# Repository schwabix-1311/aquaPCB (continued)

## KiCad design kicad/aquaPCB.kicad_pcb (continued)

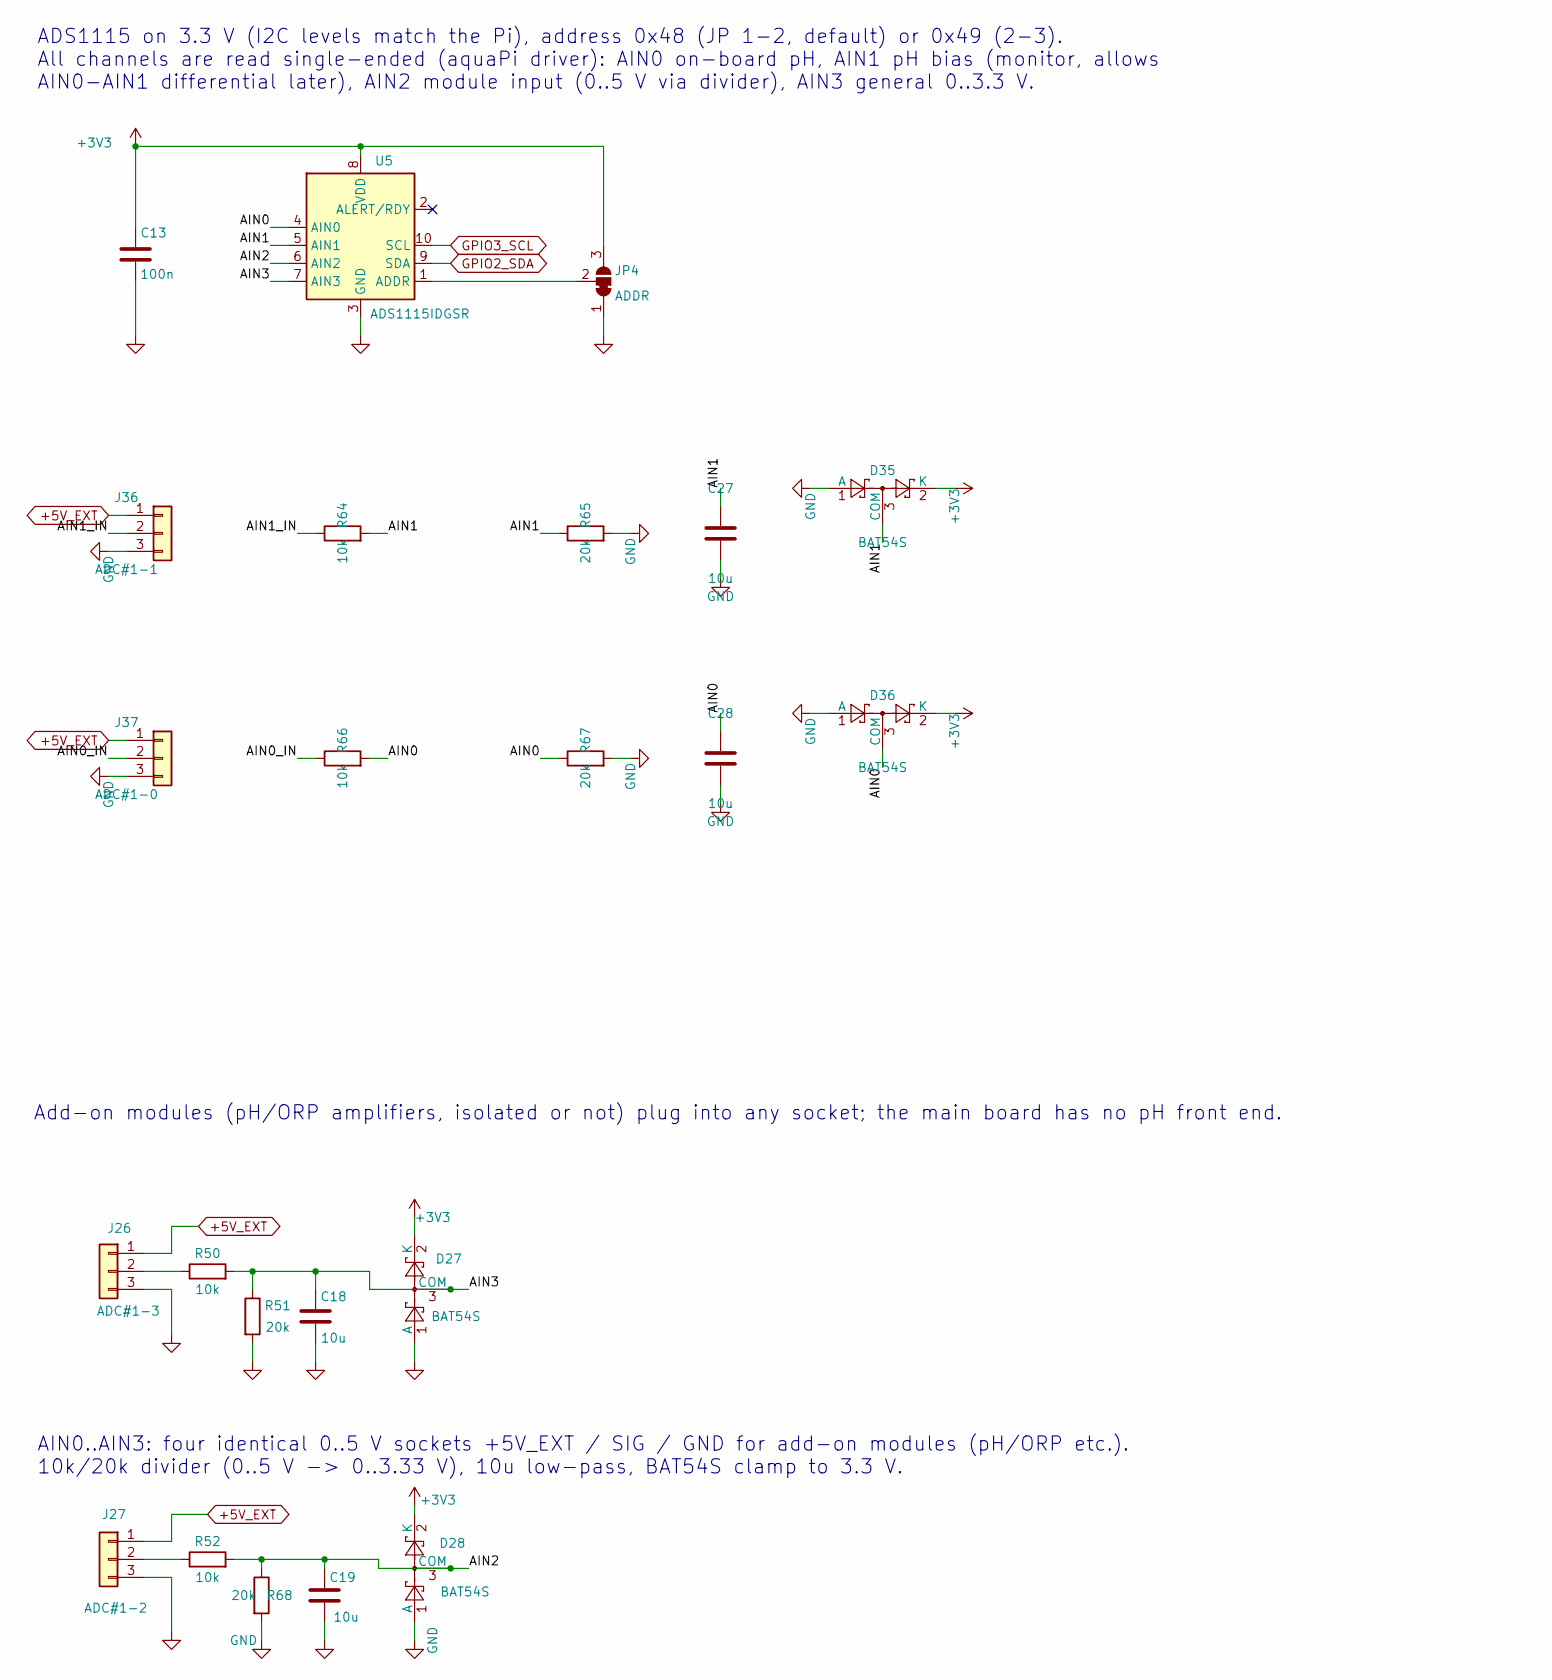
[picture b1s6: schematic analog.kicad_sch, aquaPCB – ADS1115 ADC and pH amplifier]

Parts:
C13: 100n; C_0805_2012Metric; LCSC C49678
C18, C19, C27, C28: 10u; C_0805_2012Metric; LCSC C15850
D27, D28, D35, D36: BAT54S; SOT-23; LCSC C7420333
J26: ADC#1-3; PinHeader_1x03_P2.54mm_Vertical
J27: ADC#1-2; PinHeader_1x03_P2.54mm_Vertical
J36: ADC#1-1; PinHeader_1x03_P2.54mm_Vertical
J37: ADC#1-0; PinHeader_1x03_P2.54mm_Vertical
JP4: ADDR; SolderJumper-3_P1.3mm_Bridged12_RoundedPad1.0x1.5mm
R50, R52, R64, R66: 10k; R_0805_2012Metric; LCSC C17414
R51, R65, R67, R68: 20k; R_0805_2012Metric; LCSC C4328
U5: ADS1115IDGSR; TSSOP-10_3x3mm_P0.5mm; LCSC C37593

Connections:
+3V3: C13.1, D27.2 (K), D28.2 (K), D35.2 (K), D36.2 (K), JP4.3 (B), U5.8 (VDD); also elsewhere on the board
+5V_EXT: J26.1, J27.1, J36.1, J37.1; also elsewhere on the board
/ADS1115 ADC and analog sockets/AIN0: C28.1, D36.3 (COM), R66.2, R67.1, U5.4 (AIN0)
/ADS1115 ADC and analog sockets/AIN0_IN: J37.2, R66.1
/ADS1115 ADC and analog sockets/AIN1: C27.1, D35.3 (COM), R64.2, R65.1, U5.5 (AIN1)
/ADS1115 ADC and analog sockets/AIN1_IN: J36.2, R64.1
/ADS1115 ADC and analog sockets/AIN2: C19.1, D28.3 (COM), R52.2, R68.1, U5.6 (AIN2)
/ADS1115 ADC and analog sockets/AIN3: C18.1, D27.3 (COM), R50.2, R51.1, U5.7 (AIN3)
GND: C13.2, C18.2, C19.2, C27.2, C28.2, D27.1 (A), D28.1 (A), D35.1 (A), D36.1 (A), J26.3, J27.3, J36.3, J37.3, JP4.1 (A), R51.2, R65.2, R67.2, R68.2, U5.3 (GND); also elsewhere on the board
GPIO2_SDA: U5.9 (SDA); also elsewhere on the board
GPIO3_SCL: U5.10 (SCL); also elsewhere on the board
unnamed: J26.2, R50.1
unnamed: J27.2, R52.1
unnamed: JP4.2 (C), U5.1 (ADDR)

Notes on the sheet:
AIN0..AIN3: four identical 0..5 V sockets +5V_EXT / SIG / GND for add-on modules (pH/ORP etc.). 10k/20k divider (0..5 V -> 0..3.33 V), 10u low-pass, BAT54S clamp to 3.3 V.
Add-on modules (pH/ORP amplifiers, isolated or not) plug into any socket; the main board has no pH front end.
ADS1115 on 3.3 V (I2C levels match the Pi), address 0x48 (JP 1-2, default) or 0x49 (2-3). All channels are read single-ended (aquaPi driver): AIN0 on-board pH, AIN1 pH bias (monitor, allows AIN0-AIN1 differential later), AIN2 module input (0..5 V via divider), AIN3 general 0..3.3 V.

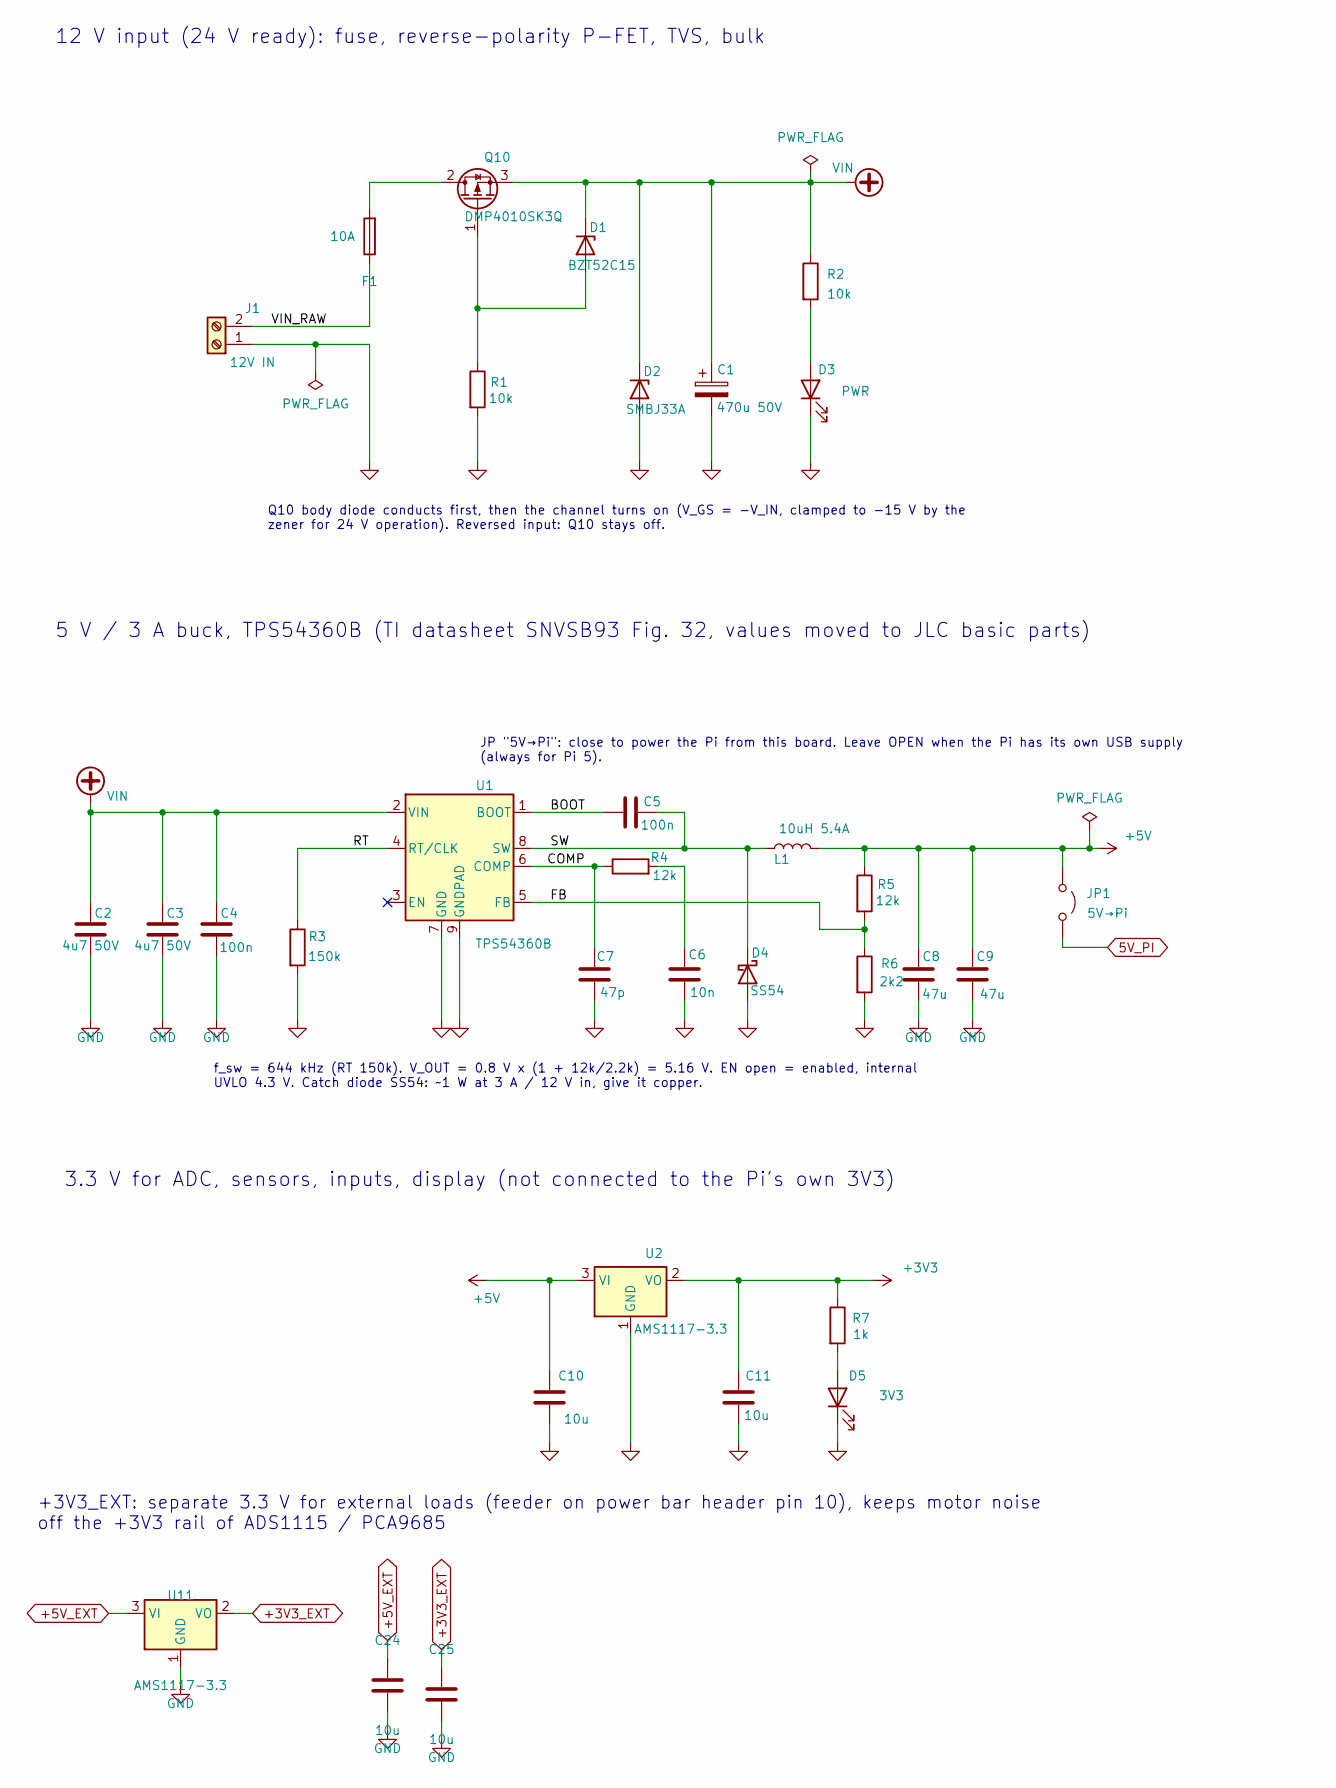
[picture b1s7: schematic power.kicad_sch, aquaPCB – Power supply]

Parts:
C1: 470u 50V; CP_Radial_D10.0mm_P5.00mm; MPN Rubycon 50ZLJ470M10X20
C2, C3: 4u7 50V; C_1206_3216Metric; LCSC C29823
C4, C5: 100n; C_0805_2012Metric; LCSC C49678
C6: 10n; C_0805_2012Metric; LCSC C1710
C7: 47p; C_0805_2012Metric; LCSC C14857
C8, C9: 47u; C_1206_3216Metric; LCSC C96123
C10, C11, C24, C25: 10u; C_0805_2012Metric; LCSC C15850
D1: BZT52C15; D_SOD-123; LCSC C19077412
D2: SMBJ33A; D_SMB; LCSC C19077586
D3: PWR; LED_0805_2012Metric; LCSC C84256
D4: SS54; D_SMA; LCSC C22452
D5: 3V3; LED_0805_2012Metric; LCSC C2297
F1: 10A; Littelfuse_OMNI-BLOK_154; LCSC C206921
J1: 12V IN; TerminalBlock_Kangnex_WJ250B-3.5-02P_P3.50mm_Staggered; LCSC C8454
JP1: 5V→Pi; PinHeader_1x02_P2.54mm_Vertical
L1: 10uH 5.4A; L_SLF12565_CDRH127; LCSC C9904
Q10: DMP4010SK3Q; TO-252-2; LCSC C5359358
R1, R2: 10k; R_0805_2012Metric; LCSC C17414
R3: 150k; R_0805_2012Metric; LCSC C17470
R4, R5: 12k; R_0805_2012Metric; LCSC C17444
R6: 2k2; R_0805_2012Metric; LCSC C17520
R7: 1k; R_0805_2012Metric; LCSC C17513
U1: TPS54360B; TI_SO-PowerPAD-8_ThermalVias; LCSC C524806
U2, U11: AMS1117-3.3; SOT-223-3_TabPin2; LCSC C6186

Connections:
5V_PI: JP1.2 (B); also elsewhere on the board
+3V3: C11.1, R7.1, U2.2 (VO); also elsewhere on the board
+3V3_EXT: C25.1, U11.2 (VO); also elsewhere on the board
+5V: C8.1, C9.1, C10.1, JP1.1 (A), L1.2, R5.1, U2.3 (VI); also elsewhere on the board
+5V_EXT: C24.1, U11.3 (VI); also elsewhere on the board
/Power supply/BOOT: C5.1, U1.1 (BOOT)
/Power supply/COMP: C7.1, R4.1, U1.6 (COMP)
/Power supply/FB: R5.2, R6.1, U1.5 (FB)
/Power supply/RT: R3.1, U1.4 (RT/CLK)
/Power supply/SW: C5.2, D4.1 (K), L1.1, U1.8 (SW)
/Power supply/VIN_RAW: F1.1, J1.2
GND: C1.2, C2.2, C3.2, C4.2, C6.2, C7.2, C8.2, C9.2, C10.2, C11.2, C24.2, C25.2, D2.2 (A), D3.1 (K), D4.2 (A), D5.1 (K), J1.1, R1.2, R3.2, R6.2, U1.7 (GND), U1.9 (GNDPAD), U2.1 (GND), U11.1 (GND); also elsewhere on the board
unnamed: C6.1, R4.2
unnamed: D1.2 (A), Q10.1 (G), R1.1
unnamed: D3.2 (A), R2.2
unnamed: D5.2 (A), R7.2
unnamed: F1.2, Q10.2 (D)
VIN: C1.1, C2.1, C3.1, C4.1, D1.1 (K), D2.1 (K), Q10.3 (S), R2.1, U1.2 (VIN); also elsewhere on the board

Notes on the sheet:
5 V / 3 A buck, TPS54360B (TI datasheet SNVSB93 Fig. 32, values moved to JLC basic parts)
f_sw = 644 kHz (RT 150k). V_OUT = 0.8 V x (1 + 12k/2.2k) = 5.16 V. EN open = enabled, internal UVLO 4.3 V. Catch diode SS54: ~1 W at 3 A / 12 V in, give it copper.
JP "5V→Pi": close to power the Pi from this board. Leave OPEN when the Pi has its own USB supply (always for Pi 5).
Q10 body diode conducts first, then the channel turns on (V_GS = -V_IN, clamped to -15 V by the zener for 24 V operation). Reversed input: Q10 stays off.
12 V input (24 V ready): fuse, reverse-polarity P-FET, TVS, bulk
3.3 V for ADC, sensors, inputs, display (not connected to the Pi's own 3V3)
+3V3_EXT: separate 3.3 V for external loads (feeder on power bar header pin 10), keeps motor noise off the +3V3 rail of ADS1115 / PCA9685

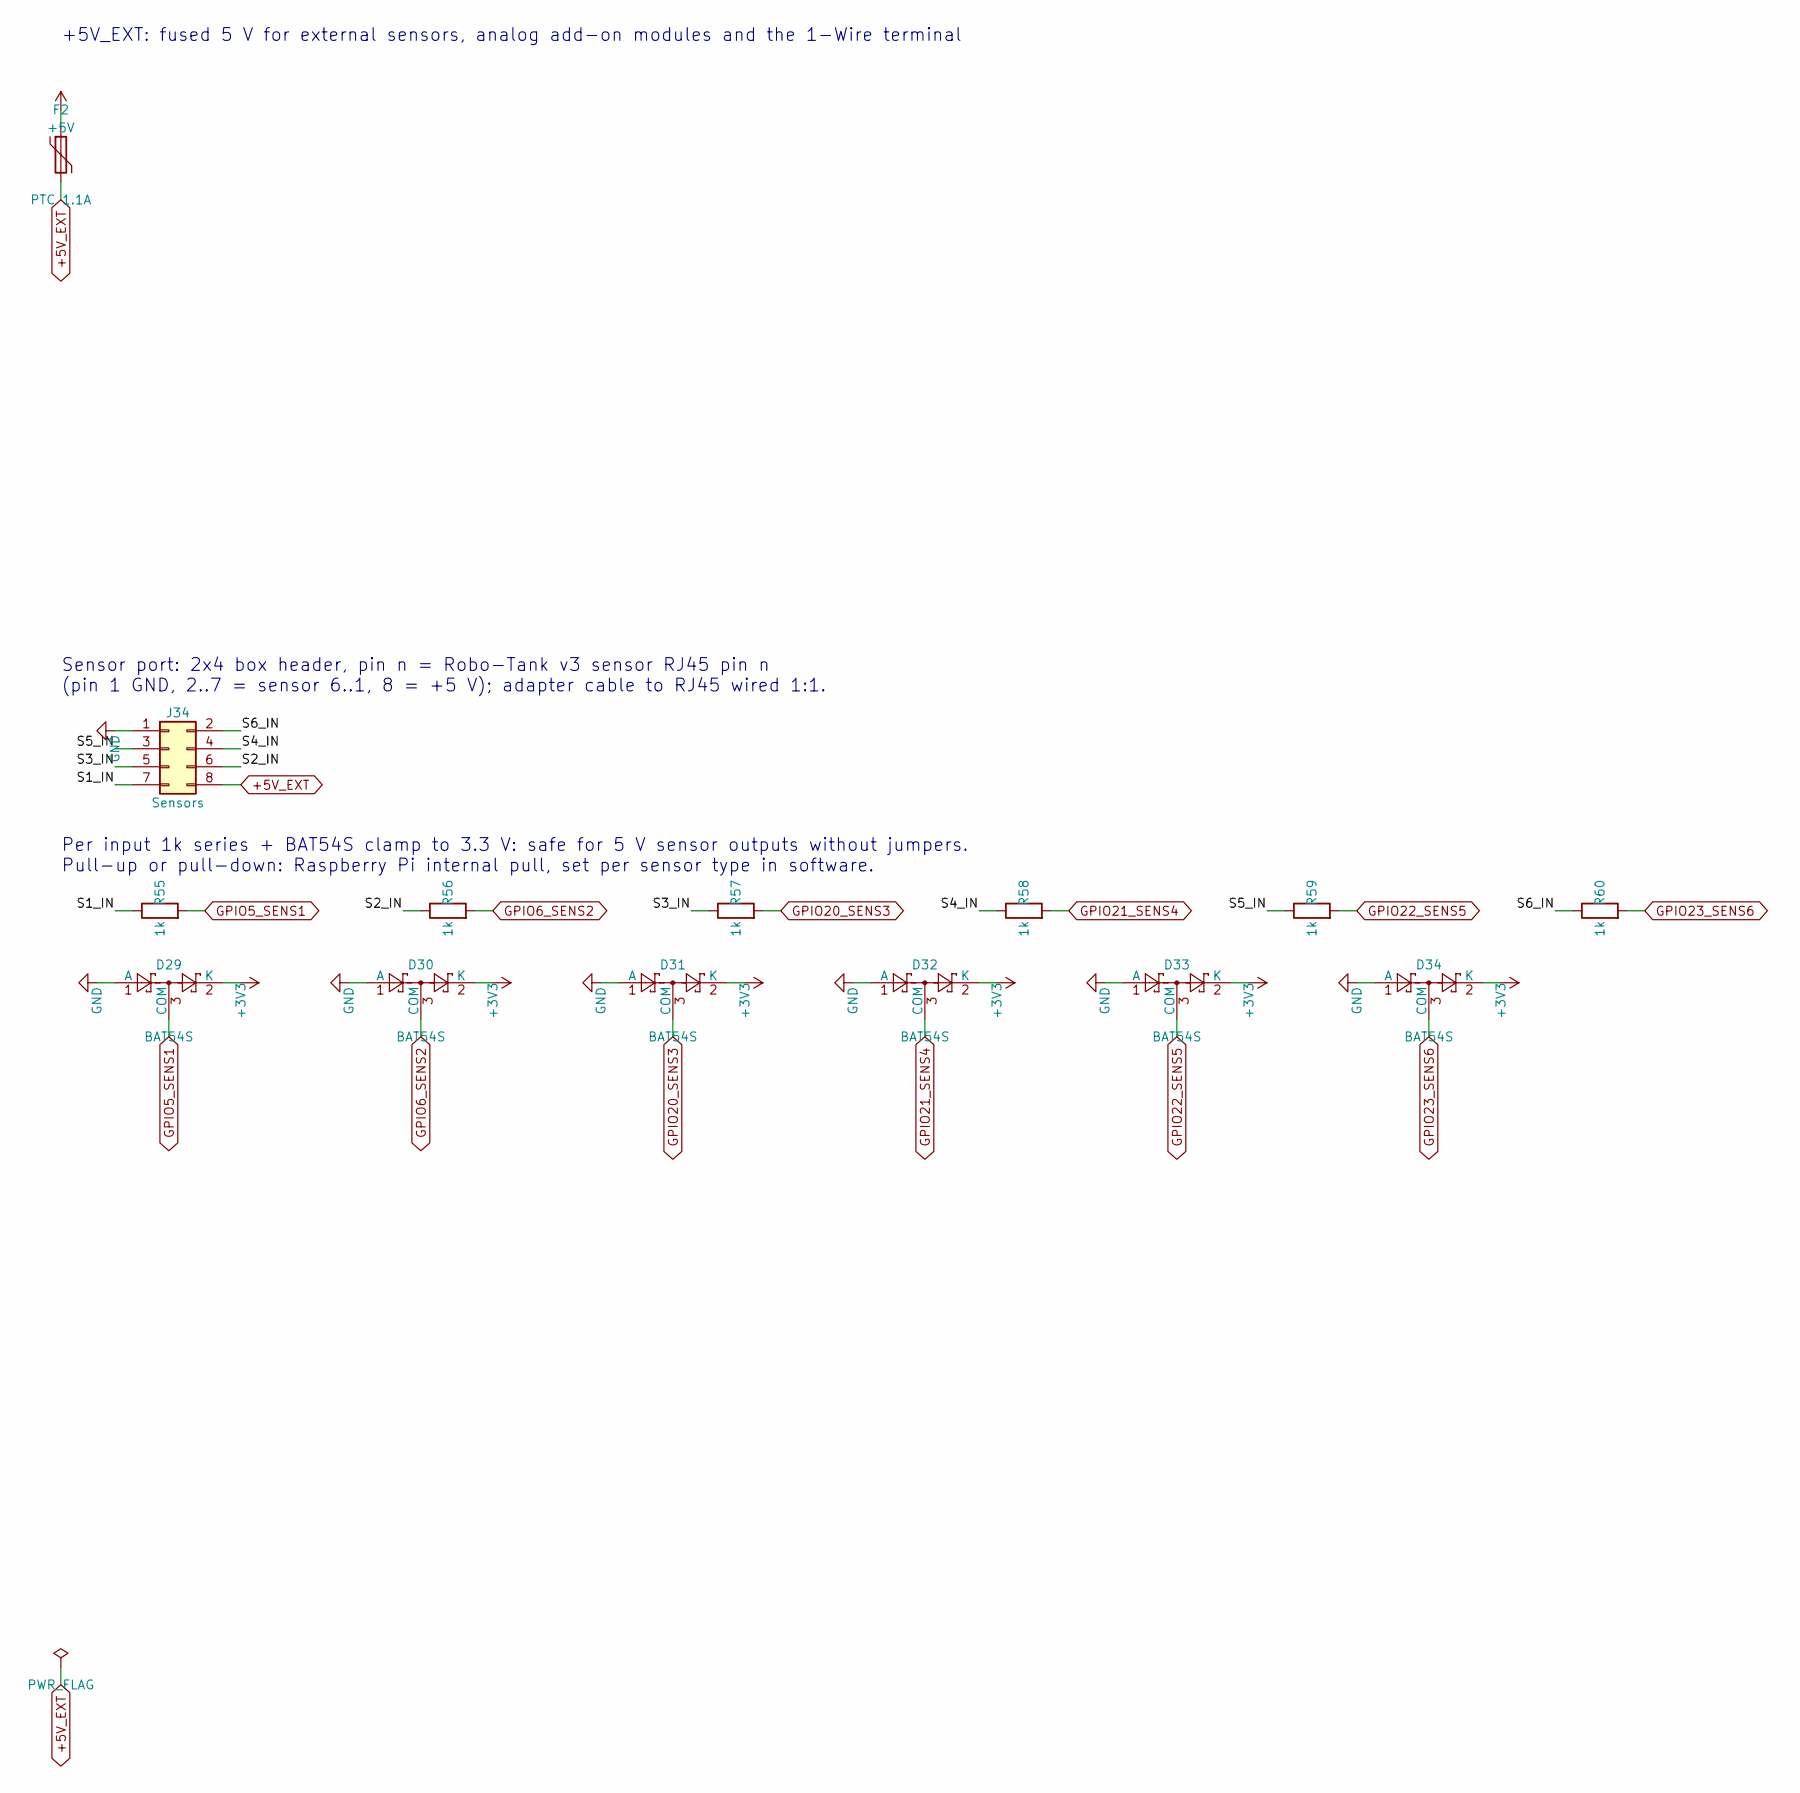
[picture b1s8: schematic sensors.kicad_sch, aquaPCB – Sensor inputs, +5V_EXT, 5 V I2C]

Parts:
D29, D30, D31, D32, D33, D34: BAT54S; SOT-23; LCSC C7420333
F2: PTC 1.1A; Fuse_1206_3216Metric; LCSC C71465
J34: Sensors; IDC-Header_2x04_P2.54mm_Vertical
R55, R56, R57, R58, R59, R60: 1k; R_0805_2012Metric; LCSC C17513

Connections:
+3V3: D29.2 (K), D30.2 (K), D31.2 (K), D32.2 (K), D33.2 (K), D34.2 (K); also elsewhere on the board
+5V: F2.1; also elsewhere on the board
+5V_EXT: F2.2, J34.8; also elsewhere on the board
/Sensor inputs, +5V_EXT/S1_IN: J34.7, R55.1
/Sensor inputs, +5V_EXT/S2_IN: J34.6, R56.1
/Sensor inputs, +5V_EXT/S3_IN: J34.5, R57.1
/Sensor inputs, +5V_EXT/S4_IN: J34.4, R58.1
/Sensor inputs, +5V_EXT/S5_IN: J34.3, R59.1
/Sensor inputs, +5V_EXT/S6_IN: J34.2, R60.1
GND: D29.1 (A), D30.1 (A), D31.1 (A), D32.1 (A), D33.1 (A), D34.1 (A), J34.1; also elsewhere on the board
GPIO5_SENS1: D29.3 (COM), R55.2; also elsewhere on the board
GPIO6_SENS2: D30.3 (COM), R56.2; also elsewhere on the board
GPIO20_SENS3: D31.3 (COM), R57.2; also elsewhere on the board
GPIO21_SENS4: D32.3 (COM), R58.2; also elsewhere on the board
GPIO22_SENS5: D33.3 (COM), R59.2; also elsewhere on the board
GPIO23_SENS6: D34.3 (COM), R60.2; also elsewhere on the board

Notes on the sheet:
+5V_EXT: fused 5 V for external sensors, analog add-on modules and the 1-Wire terminal
Sensor port: 2x4 box header, pin n = Robo-Tank v3 sensor RJ45 pin n (pin 1 GND, 2..7 = sensor 6..1, 8 = +5 V); adapter cable to RJ45 wired 1:1.
Per input 1k series + BAT54S clamp to 3.3 V: safe for 5 V sensor outputs without jumpers. Pull-up or pull-down: Raspberry Pi internal pull, set per sensor type in software.

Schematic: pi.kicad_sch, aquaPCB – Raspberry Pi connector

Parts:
H1, H2, H3, H4: M3; MountingHole_3.2mm_M3
H5, H6: M2.5 Pi Zero; MountingHole_2.7mm_M2.5
J2: Raspberry Pi; IDC-Header_2x20_P2.54mm_Vertical

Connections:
5V_PI: J2.2, J2.4; also elsewhere on the board
GND: J2.6, J2.9, J2.14, J2.20, J2.25, J2.30, J2.34, J2.39; also elsewhere on the board
GPIO2_SDA: J2.3; also elsewhere on the board
GPIO3_SCL: J2.5; also elsewhere on the board
GPIO4_1W: J2.7; also elsewhere on the board
GPIO5_SENS1: J2.29; also elsewhere on the board
GPIO6_SENS2: J2.31; also elsewhere on the board
GPIO7_CE1: J2.26; also elsewhere on the board
GPIO8_CE0: J2.24; also elsewhere on the board
GPIO9_MISO: J2.21; also elsewhere on the board
GPIO10_MOSI: J2.19; also elsewhere on the board
GPIO11_SCLK: J2.23; also elsewhere on the board
GPIO12_Q6: J2.32; also elsewhere on the board
GPIO13_Q5: J2.33; also elsewhere on the board
GPIO16_Q2: J2.36; also elsewhere on the board
GPIO18_Q1: J2.12; also elsewhere on the board
GPIO19_Q4: J2.35; also elsewhere on the board
GPIO20_SENS3: J2.38; also elsewhere on the board
GPIO21_SENS4: J2.40; also elsewhere on the board
GPIO22_SENS5: J2.15; also elsewhere on the board
GPIO23_SENS6: J2.16; also elsewhere on the board
GPIO24_DISP_RST: J2.18; also elsewhere on the board
GPIO25_DISP_DC: J2.22; also elsewhere on the board
GPIO26_Q3: J2.37; also elsewhere on the board

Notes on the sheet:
40-pin Pi header, normal (not mirrored) numbering. Fit 2x20 socket (Pi Zero 2 W face-up, header soldered on its underside) or 40-pin box header (Pi 3/4 via IDC ribbon).
Pins 1/17 (Pi 3V3) stay unconnected: this board has its own 3.3 V regulator. Pins 27/28 (ID EEPROM) unused. GPIO 14/15 only go to the UART console header.

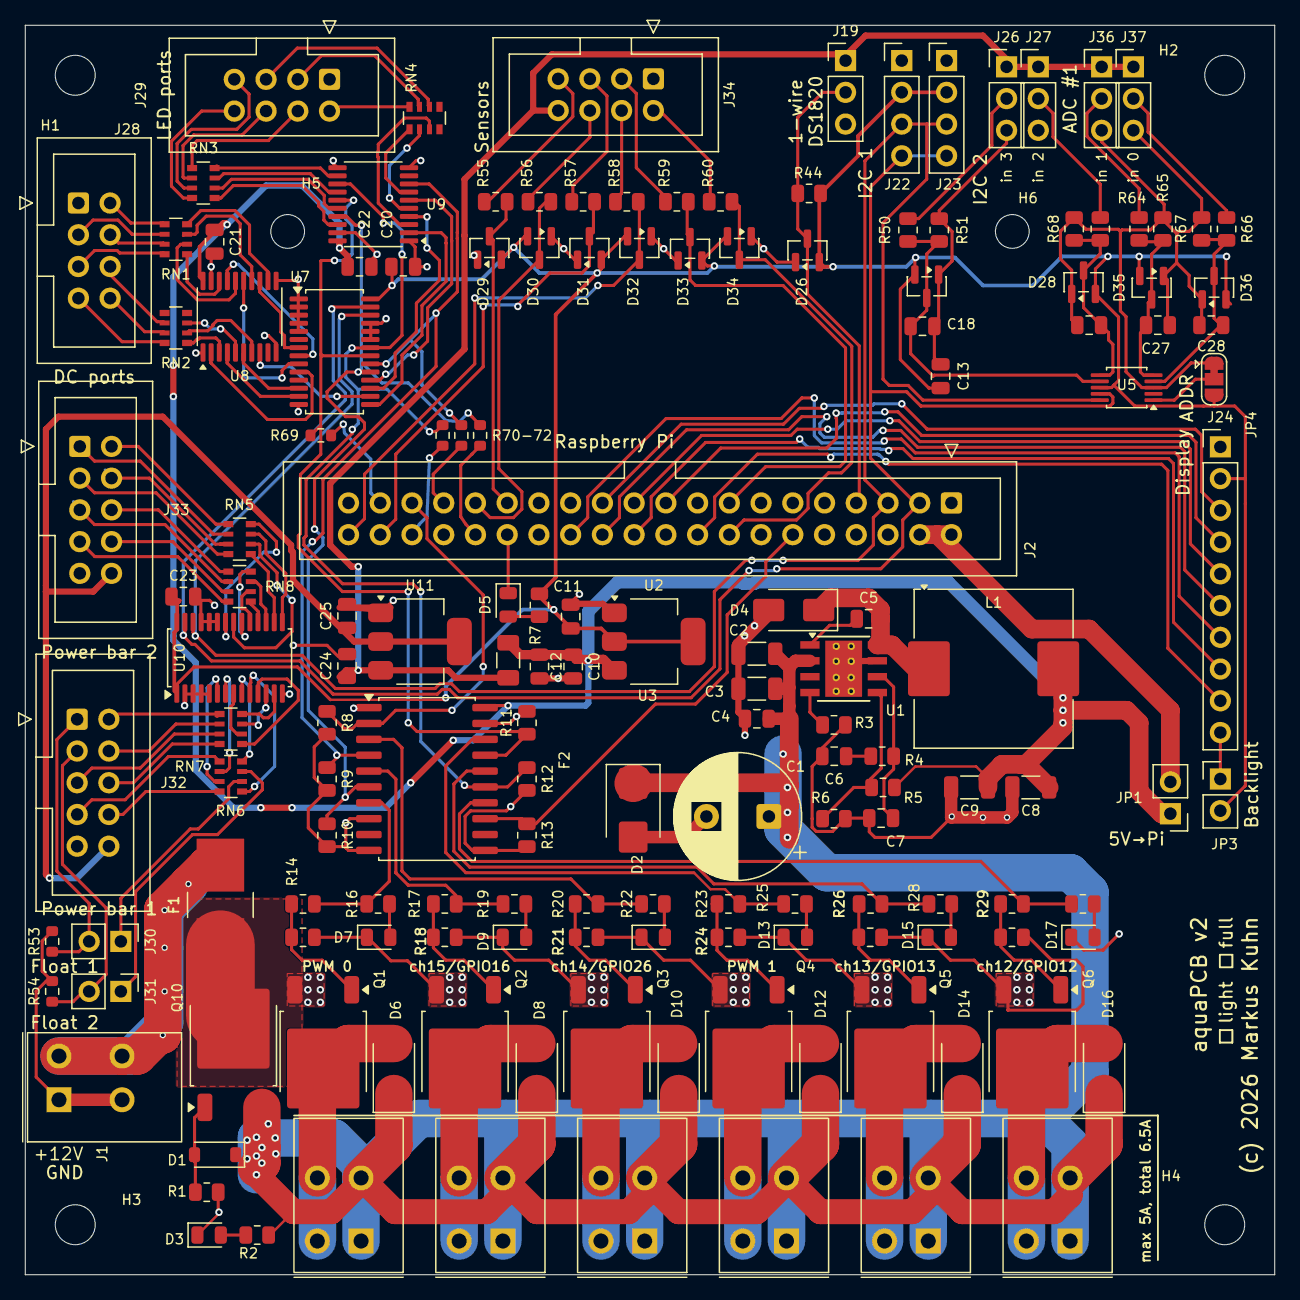
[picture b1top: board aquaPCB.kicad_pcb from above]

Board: 2 copper layers, 100.0 x 100.0 mm, 162 parts (0 on the bottom side), 156 nets.

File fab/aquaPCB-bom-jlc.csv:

Comment,Designator,Footprint,LCSC Part #
4u7 50V,"C2,C3",C_1206_3216Metric,C29823
100n,"C4,C5,C12,C13,C20,C21,C22,C23",C_0805_2012Metric,C49678
10n,C6,C_0805_2012Metric,C1710
47p,C7,C_0805_2012Metric,C14857
47u,"C8,C9",C_1206_3216Metric,C96123
10u,"C10,C11,C18,C19,C24,C25,C27,C28",C_0805_2012Metric,C15850
BZT52C15,D1,D_SOD-123,C19077412
SMBJ33A,D2,D_SMB,C19077586
PWR,D3,LED_0805_2012Metric,C84256
SS54,"D4,D6,D8,D10,D12,D14,D16",D_SMA,C22452
3V3,D5,LED_0805_2012Metric,C2297
GPIO18,D7,LED_0805_2012Metric,C2297
PCA#1 ch15,D9,LED_0805_2012Metric,C2297
PCA#1 ch14,D11,LED_0805_2012Metric,C2297
GPIO19,D13,LED_0805_2012Metric,C2297
PCA#1 ch13,D15,LED_0805_2012Metric,C2297
PCA#1 ch12,D17,LED_0805_2012Metric,C2297
BAT54S,"D26,D27,D28,D29,D30,D31,D32,D33,D34,D35,D36",SOT-23,C7420333
10A,F1,Littelfuse_OMNI-BLOK_154,C206921
PTC 1.1A,F2,Fuse_1206_3216Metric,C71465
10uH 5.4A,L1,L_SLF12565_CDRH127,C9904
AOD4184A,"Q1,Q2,Q3,Q4,Q5,Q6",TO-252-2,C99124
DMP4010SK3Q,Q10,TO-252-2,C5359358
10k,"R1,R2,R8,R9,R10,R11,R12,R13,R15,R18,R21,R24,R27,R30,R50,R52,R64,R66",R_0805_2012Metric,C17414
150k,R3,R_0805_2012Metric,C17470
12k,"R4,R5",R_0805_2012Metric,C17444
2k2,R6,R_0805_2012Metric,C17520
1k,"R7,R16,R19,R22,R25,R28,R31,R55,R56,R57,R58,R59,R60",R_0805_2012Metric,C17513
100,"R14,R17,R20,R23,R26,R29",R_0805_2012Metric,C17408
4k7,R44,R_0805_2012Metric,C17673
20k,"R51,R65,R67,R68",R_0805_2012Metric,C4328
10k,"R53,R54",R_0603_1608Metric,C25804
4x100,"RN1,RN2,RN3,RN4,RN5,RN6,RN7,RN8",R_Array_Convex_4x0603,C25506
TPS54360B,U1,TI_SO-PowerPAD-8_ThermalVias,C524806
AMS1117-3.3,"U2,U11",SOT-223-3_TabPin2,C6186
74HCT244D,U3,SOIC-20W_7.5x12.8mm_P1.27mm,C5978
ADS1115IDGSR,U5,TSSOP-10_3x3mm_P0.5mm,C37593
PCA9685PW,"U7,U10",TSSOP-28_4.4x9.7mm_P0.65mm,C2678753
74HCT244PW,"U8,U9",TSSOP-20_4.4x6.5mm_P0.65mm,C131088

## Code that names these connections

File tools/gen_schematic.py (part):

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sh.note('40-pin Pi header, normal (not mirrored) numbering. Fit 2x20 socket (Pi Zero 2 W face-up, header\n'
        'soldered on its underside) or 40-pin box header (Pi 3/4 via IDC ribbon).', 2)
pi_pins = {
    1: NC, 2: '5V_PI', 3: 'GPIO2_SDA', 4: '5V_PI', 5: 'GPIO3_SCL', 6: 'GND', 7: 'GPIO4_1W', 8: 'GPIO14_TXD',
    9: 'GND', 10: 'GPIO15_RXD', 11: 'GPIO17_S1', 12: 'GPIO18_Q1', 13: 'GPIO27_S4', 14: 'GND',
    15: 'GPIO22_S2', 16: 'GPIO23_S3', 17: NC, 18: 'GPIO24_DISP_RST', 19: 'GPIO10_MOSI', 20: 'GND',
    21: 'GPIO9_MISO', 22: 'GPIO25_DISP_DC', 23: 'GPIO11_SCLK', 24: 'GPIO8_CE0', 25: 'GND', 26: 'GPIO7_CE1',
    27: NC, 28: NC, 29: 'GPIO5_IN1', 30: 'GND', 31: 'GPIO6_IN2', 32: 'GPIO12_Q3', 33: 'GPIO13_Q4', 34: 'GND',
    35: 'GPIO19_Q2', 36: 'GPIO16_Q5', 37: 'GPIO26_Q6', 38: 'GPIO20_IN3', 39: 'GND', 40: 'GPIO21_IN4'}
jpi = sh.part('Connector_Generic:Conn_02x20_Odd_Even', 'J', 'Raspberry Pi',
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# ================================================================ Power outputs
sh = p.sheet('outputs', 'outputs.kicad_sch', 'Power outputs Q1..Q6')
sh.note('74HCT244 shifts 3.3 V GPIO to 5 V gate drive and isolates the Pi from the power stage.', 2)
gpio_q = ['GPIO18_Q1', 'GPIO19_Q2', 'GPIO12_Q3', 'GPIO13_Q4', 'GPIO16_Q5', 'GPIO26_Q6']
buf = sh.part('74xx:74HCT244', 'U', '74HCT244D', {
    '1': 'GND', '19': 'GND', '20': '+5V', '10': 'GND',
    '2': gpio_q[0], '4': gpio_q[1], '6': gpio_q[2], '8': gpio_q[3],
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    rp = R(sh, '10k', '+3V3', g)
    sh.row([t, rs, rp, clamp(sh, g)])
sh.note('1-Wire (DS18B20), GPIO4, 4.7k pull-up. Terminal: GND / DQ / 3V3; parasitic sensors use GND + DQ.', 2)
r1w = R(sh, '4k7', '+3V3', 'GPIO4_1W')
terms = [term(sh, ['GND', 'GPIO4_1W', '+3V3'], f'1-Wire {i}') for i in range(1, 3)]
sh.row([r1w, clamp(sh, 'GPIO4_1W')] + terms)
sh.note('I2C expansion (OLED, PCA9685, ...), SSD1306 pin order. Pull-ups are on the Pi (1.8k).', 2)
i2c = [header(sh, ['GND', '+3V3', 'GPIO3_SCL', 'GPIO2_SDA'], f'I2C {i}') for i in (1, 2)]
sh.row(i2c)
sh.note('SPI display (ST7735 / ILI9341). Backlight to 3V3 via jumper.', 2)
disp = header(sh, ['GND', '+3V3', 'GPIO11_SCLK', 'GPIO10_MOSI', 'GPIO9_MISO', 'GPIO8_CE0', 'GPIO7_CE1',
                   'GPIO25_DISP_DC', 'GPIO24_DISP_RST', 'DISP_BL'], 'Display')
jbl = sh.part('Jumper:Jumper_2_Open', 'JP', 'Backlight', {'1': '+3V3', '2': 'DISP_BL'}, fp=hdr(2),
              fields={REICHELT: 'ECON SL40G1 (cut) + JUMPER 2,54 SW'})
sh.row([disp, jbl])
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        'AIN0-AIN1 differential later), AIN2 module input (0..5 V via divider), AIN3 general 0..3.3 V.', 2)
adc = sh.part('Analog_ADC:ADS1115IDGS', 'U', 'ADS1115IDGSR', {
    '1': 'ADS_ADDR', '2': NC, '3': 'GND', '4': 'PH_SIG', '5': 'PH_REF', '6': 'AIN2', '7': 'AIN3',
    '8': '+3V3', '9': 'GPIO2_SDA', '10': 'GPIO3_SCL'}, lcsc='C37593')
cadc = C(sh, '100n', '+3V3', 'GND')
jaddr = sh.part('Jumper:SolderJumper_3_Bridged12', 'JP', 'ADDR', {'1': 'GND', '2': 'ADS_ADDR', '3': '+3V3'},
                fp='Jumper:SolderJumper-3_P1.3mm_Bridged12_RoundedPad1.0x1.5mm')
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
